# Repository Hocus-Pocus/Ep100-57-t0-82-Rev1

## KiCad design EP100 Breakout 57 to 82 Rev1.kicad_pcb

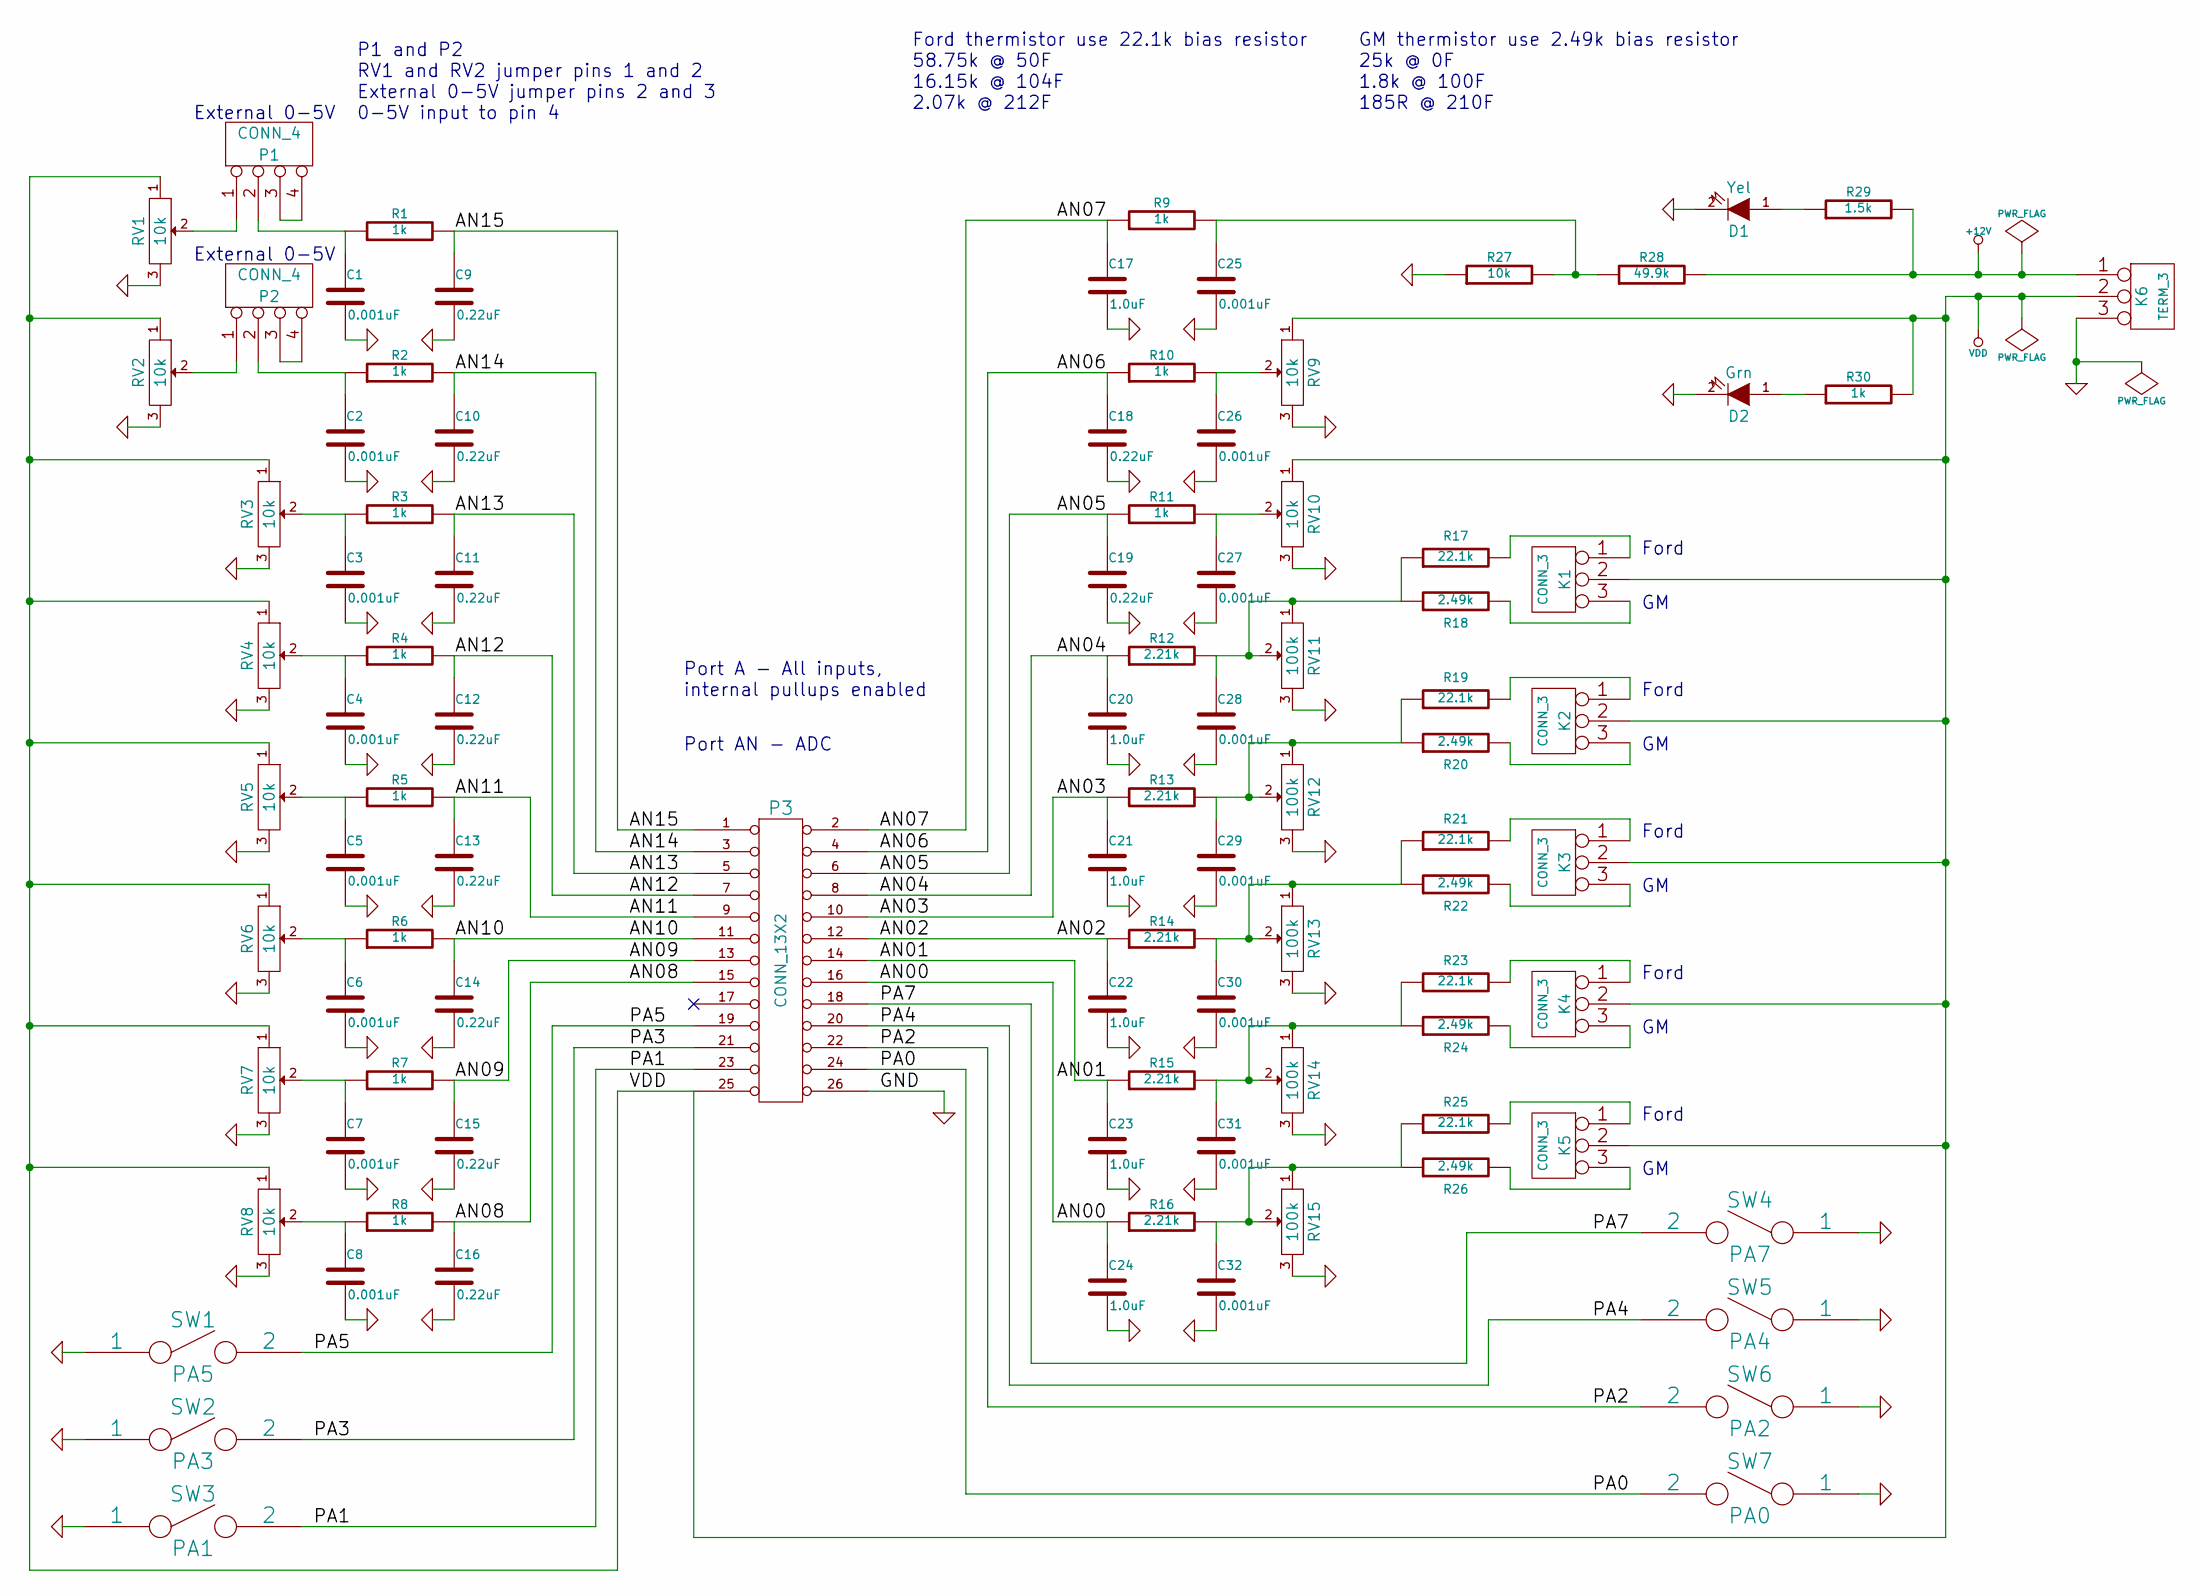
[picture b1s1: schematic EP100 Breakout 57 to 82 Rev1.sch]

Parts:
C1, C2, C3, C4, C5, C6, C7, C8, C25, C26, C27, C28, C29, C30, C31, C32: 0.001uF
C9, C10, C11, C12, C13, C14, C15, C16, C18, C19: 0.22uF
C17, C20, C21, C22, C23, C24: 1.0uF
D1: Yel
D2: Grn
K1, K2, K3, K4, K5: CONN_3
K6: TERM_3
P1, P2: CONN_4
P3: CONN_13X2
R1, R2, R3, R4, R5, R6, R7, R8, R9, R10, R11, R30: 1k
R12, R13, R14, R15, R16: 2.21k
R17, R19, R21, R23, R25: 22.1k
R18, R20, R22, R24, R26: 2.49k
R27: 10k
R28: 49.9k
R29: 1.5k
RV1, RV2, RV3, RV4, RV5, RV6, RV7, RV8, RV9, RV10: 10k
RV11, RV12, RV13, RV14, RV15: 100k
SW1: PA5
SW2: PA3
SW3: PA1
SW4: PA7
SW5: PA4
SW6: PA2
SW7: PA0

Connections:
+12V: K6.1, R28.2, R29.2
/AN00: C24.1, P3.16, R16.1
/AN01: C23.1, P3.14, R15.1
/AN02: C22.1, P3.12, R14.1
/AN03: C21.1, P3.10, R13.1
/AN04: C20.1, P3.8, R12.1
/AN05: C19.1, P3.6, R11.1
/AN06: C18.1, P3.4, R10.1
/AN07: C17.1, P3.2, R9.1
/AN08: C16.1, P3.15, R8.2
/AN09: C15.1, P3.13, R7.2
/AN10: C14.1, P3.11, R6.2
/AN11: C13.1, P3.9, R5.2
/AN12: C12.1, P3.7, R4.2
/AN13: C11.1, P3.5, R3.2
/AN14: C10.1, P3.3, R2.2
/AN15: C9.1, P3.1, R1.2
/PA0: P3.24 (P20), SW7.2
/PA1: P3.23, SW3.2
/PA2: P3.22, SW6.2
/PA3: P3.21, SW2.2
/PA4: P3.20, SW5.2
/PA5: P3.19, SW1.2
/PA7: P3.18, SW4.2
GND: C1.2, C2.2, C3.2, C4.2, C5.2, C6.2, C7.2, C8.2, C9.2, C10.2, C11.2, C12.2, C13.2, C14.2, C15.2, C16.2, C17.2, C18.2, C19.2, C20.2, C21.2, C22.2, C23.2, C24.2, C25.2, C26.2, C27.2, C28.2, C29.2, C30.2, C31.2, C32.2, D1.2 (K), D2.2 (K), K6.3, P3.26, R27.1, RV1.3, RV2.3, RV3.3, RV4.3, RV5.3, RV6.3, RV7.3, RV8.3, RV9.3, RV10.3, RV11.3, RV12.3, RV13.3, RV14.3, RV15.3, SW1.1, SW2.1, SW3.1, SW4.1, SW5.1, SW6.1, SW7.1
unnamed: C25.1, R9.2, R27.2, R28.1
unnamed: D2.1 (A), R30.1
unnamed: D1.1 (A), R29.1
unnamed: C7.1, R7.1, RV7.2
unnamed: C5.1, R5.1, RV5.2
unnamed: C4.1, R4.1, RV4.2
unnamed: C3.1, R3.1, RV3.2
unnamed: P2.1, RV2.2
unnamed: C2.1, P2.2, R2.1
unnamed: P2.3, P2.4
unnamed: P1.1, RV1.2
unnamed: C1.1, P1.2, R1.1
unnamed: P1.3, P1.4
unnamed: C8.1, R8.1, RV8.2
unnamed: C26.1, R10.2, RV9.2
unnamed: C27.1, R11.2, RV10.2
unnamed: C32.1, R16.2, R25.1, R26.1, RV15.1, RV15.2
unnamed: C6.1, R6.1, RV6.2
unnamed: K3.1, R21.2
unnamed: K3.3, R22.2
unnamed: C30.1, R14.2, R21.1, R22.1, RV13.1, RV13.2
unnamed: C29.1, R13.2, R19.1, R20.1, RV12.1, RV12.2
unnamed: K2.1, R19.2
unnamed: K2.3, R20.2
unnamed: K4.3, R24.2
unnamed: C31.1, R15.2, R23.1, R24.1, RV14.1, RV14.2
unnamed: K4.1, R23.2
unnamed: C28.1, R12.2, R17.1, R18.1, RV11.1, RV11.2
unnamed: K1.1, R17.2
unnamed: K1.3, R18.2
unnamed: K5.1, R25.2
unnamed: K5.3, R26.2
VDD: K1.2 (PM), K2.2 (PM), K3.2 (PM), K4.2 (PM), K5.2 (PM), K6.2 (PM), P3.25, R30.2, RV1.1, RV2.1, RV3.1, RV4.1, RV5.1, RV6.1, RV7.1, RV8.1, RV9.1, RV10.1

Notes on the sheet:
Ford
Ford thermistor use 22.1k bias resistor 58.75k @ 50F 16.15k @ 104F 2.07k @ 212F
GM thermistor use 2.49k bias resistor 25k @ 0F 1.8k @ 100F 185R @ 210F
External 0-5V
Port AN - ADC
Port A - All inputs, internal pullups enabled
P1 and P2 RV1 and RV2 jumper pins 1 and 2 External 0-5V jumper pins 2 and 3 0-5V input to pin 4

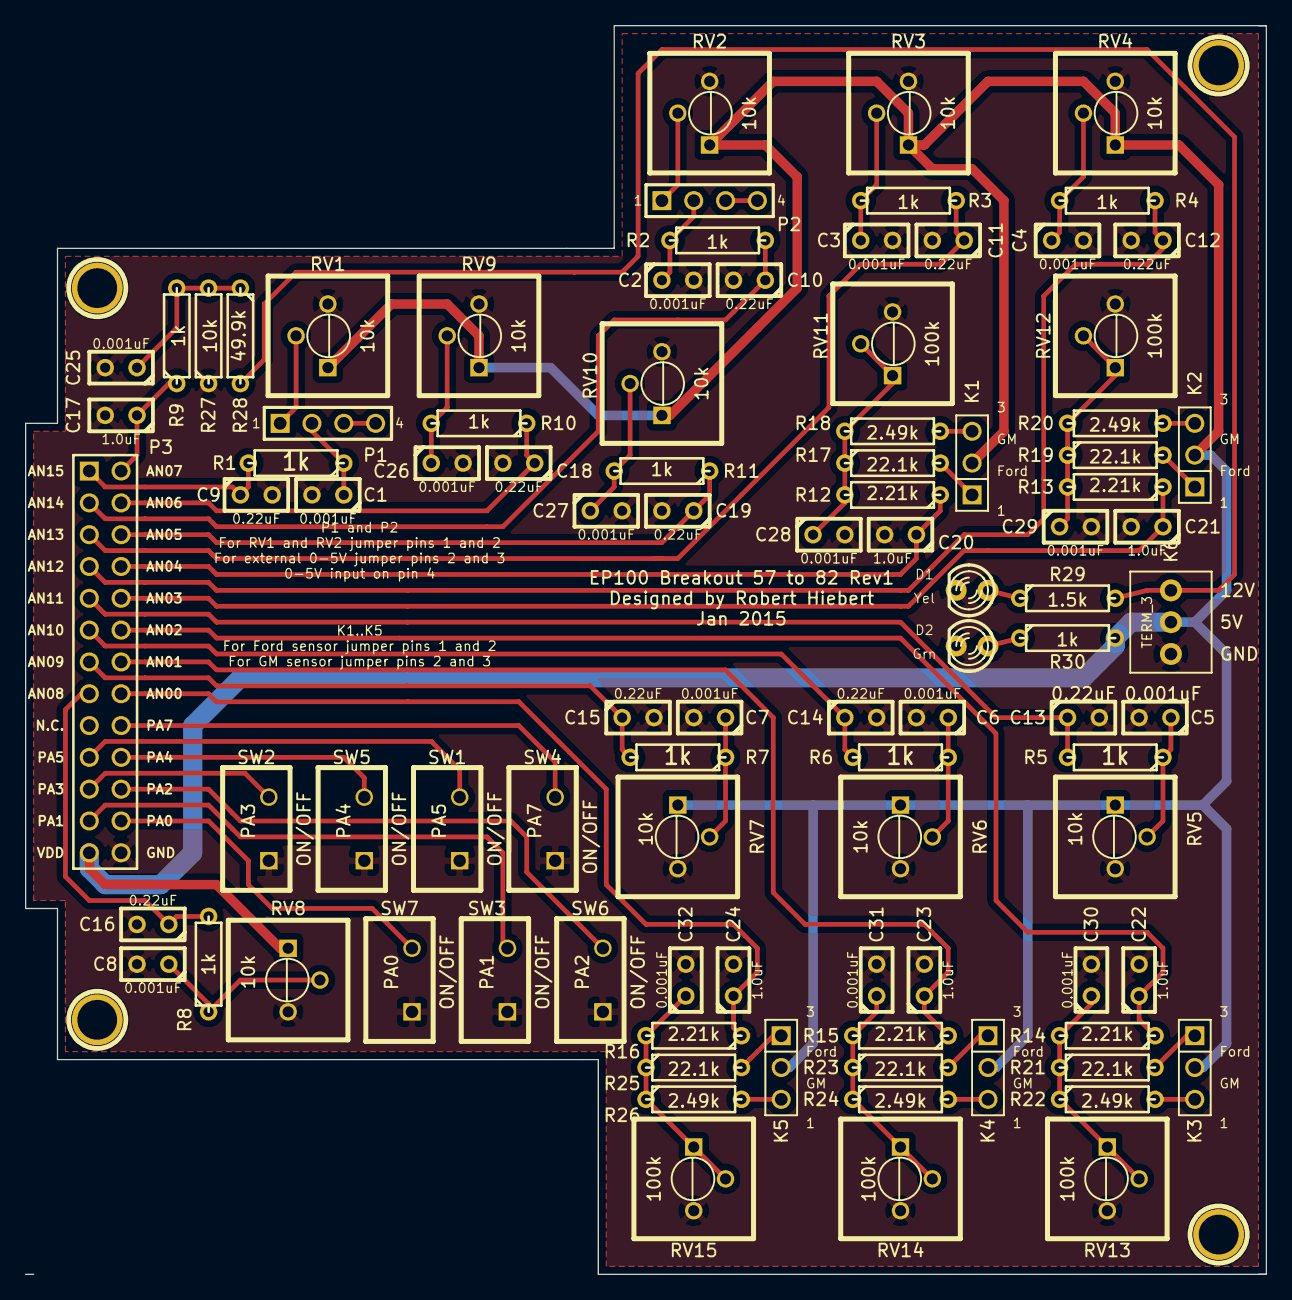
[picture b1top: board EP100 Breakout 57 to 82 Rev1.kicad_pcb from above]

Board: 2 copper layers, 99.1 x 99.7 mm, 99 parts (0 on the bottom side), 58 nets.

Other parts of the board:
Hole .125, Hole .125#2, Hole .125#3, Hole .125#4: P***; Hole.125
